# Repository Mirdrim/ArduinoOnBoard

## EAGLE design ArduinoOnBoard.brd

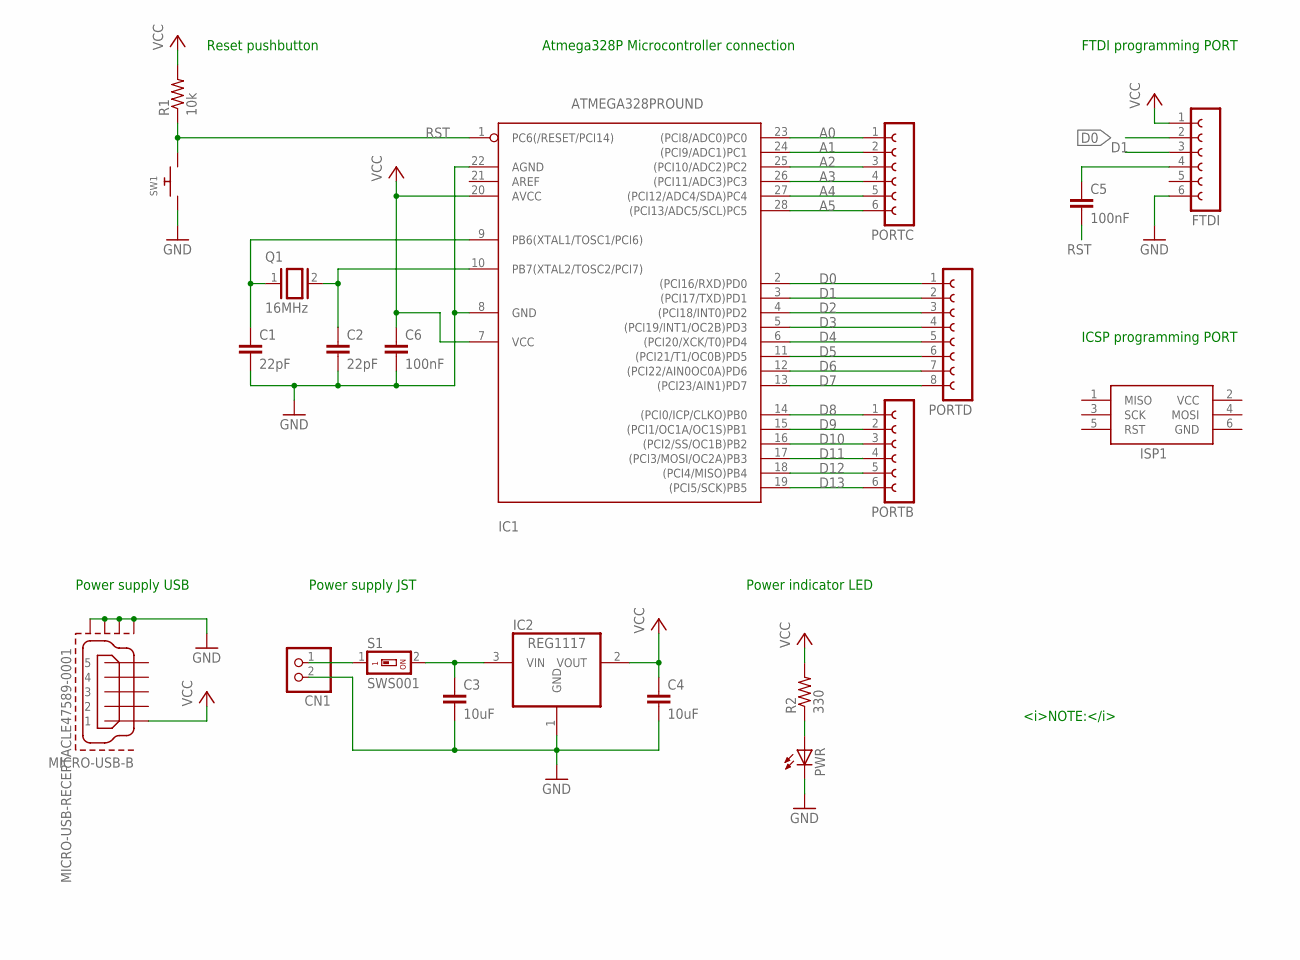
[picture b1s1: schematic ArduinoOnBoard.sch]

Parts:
C1, C2: 22pF; C1310
C3, C4: 10uF; C1310
C5, C6: 100nF; C1310
CN1: JST_2PIN-SMT; JST-PH-2-SMT
FTDI: FE06-1; FE06
IC1: ATMEGA328PROUND; DIL28-3-ROUND
IC2: REG1117; SOT223
ISP1: AVRISP-6; AVRISP
MICRO-USB-B: MICRO-USB-RECEPTACLE47589-0001; 47589-0001
PORTB: FE06-1; FE06
PORTC: FE06-1; FE06
PORTD: FE08-1; FE08
PWR: LEDCHIPLED_0805; CHIPLED_0805
Q1: 16MHz; QS
R1: 10k; M1206
R2: 330; M1206
S1: SWS001; SMS-001
SW1: SWITCH_PUSHBUTTONEVQ-PE; TACT_PANA-EVQ

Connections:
A0: IC1.23 ((PCI8/ADC0)PC0), PORTC.1
A1: IC1.24 ((PCI9/ADC1)PC1), PORTC.2
A2: IC1.25 ((PCI10/ADC2)PC2), PORTC.3
A3: IC1.26 ((PCI11/ADC3)PC3), PORTC.4
A4: IC1.27 ((PCI12/ADC4/SDA)PC4), PORTC.5
A5: IC1.28 ((PCI13/ADC5/SCL)PC5), PORTC.6
D0: FTDI.2, IC1.2 ((PCI16/RXD)PD0), PORTD.1
D1: FTDI.3, IC1.3 ((PCI17/TXD)PD1), PORTD.2
D2: IC1.4 ((PCI18/INT0)PD2), PORTD.3
D3: IC1.5 ((PCI19/INT1/OC2B)PD3), PORTD.4
D4: IC1.6 ((PCI20/XCK/T0)PD4), PORTD.5
D5: IC1.11 ((PCI21/T1/OC0B)PD5), PORTD.6
D6: IC1.12 ((PCI22/AIN0OC0A)PD6), PORTD.7
D7: IC1.13 ((PCI23/AIN1)PD7), PORTD.8
D8: IC1.14 ((PCI0/ICP/CLKO)PB0), PORTB.1
D9: IC1.15 ((PCI1/OC1A/OC1S)PB1), PORTB.2
D10: IC1.16 ((PCI2/SS/OC1B)PB2), PORTB.3
D11: IC1.17 ((PCI3/MOSI/OC2A)PB3), PORTB.4
D12: IC1.18 ((PCI4/MISO)PB4), PORTB.5
D13: IC1.19 ((PCI5/SCK)PB5), PORTB.6
GND: C1.2, C2.2, C3.2, C4.2, C6.2, CN1.2 (1), FTDI.6, IC1.8 (GND), IC1.22 (AGND), IC2.1 (GND), ISP1.6 (GND), MICRO-USB-B.CASING1 (GND1), MICRO-USB-B.CASING2 (GND2), MICRO-USB-B.CASING3 (GND3), MICRO-USB-B.CASING4 (GND4), PWR.C, SW1.P$1
unnamed: C5.1, FTDI.4
unnamed: C1.1, IC1.9 (PB6(XTAL1/TOSC1/PCI6)), Q1.1
unnamed: C2.1, IC1.10 (PB7(XTAL2/TOSC2/PCI7)), Q1.2
unnamed: C3.1, IC2.3 (VIN), S1.2
unnamed: PWR.A, R2.1
unnamed: CN1.1 (2), S1.1
RST: C5.2, IC1.1 (PC6(/RESET/PCI14)), R1.1, SW1.P$2
VCC: C4.1, C6.1, FTDI.1, IC1.7 (VCC), IC1.20 (AVCC), IC2.2 (VOUT), ISP1.2 (VCC), MICRO-USB-B.1, R1.2, R2.2

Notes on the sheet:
Power supply USB
Power supply JST
Reset pushbutton
Power indicator LED
FTDI programming PORT
Atmega328P Microcontroller connection
<i>NOTE:</i>
ICSP programming PORT

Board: 2 copper layers, 21 parts (0 on the bottom side), 29 nets, no tracks yet.

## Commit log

2018-02-16 Information
    Information of the project
2018-03-13 Eagle/
2018-03-13 Eagle files
    Schematics and PCB layout
2018-03-13 Eagle files
    Schematics and PCB layouts
2018-03-13 Eagle files commit

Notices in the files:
parts and their libraries:
con-molex-usb: (C) 2014 Tomasz Boleslaw CEDRO, cederom@tlen.pl, http://www.tomek.cedro.info.
